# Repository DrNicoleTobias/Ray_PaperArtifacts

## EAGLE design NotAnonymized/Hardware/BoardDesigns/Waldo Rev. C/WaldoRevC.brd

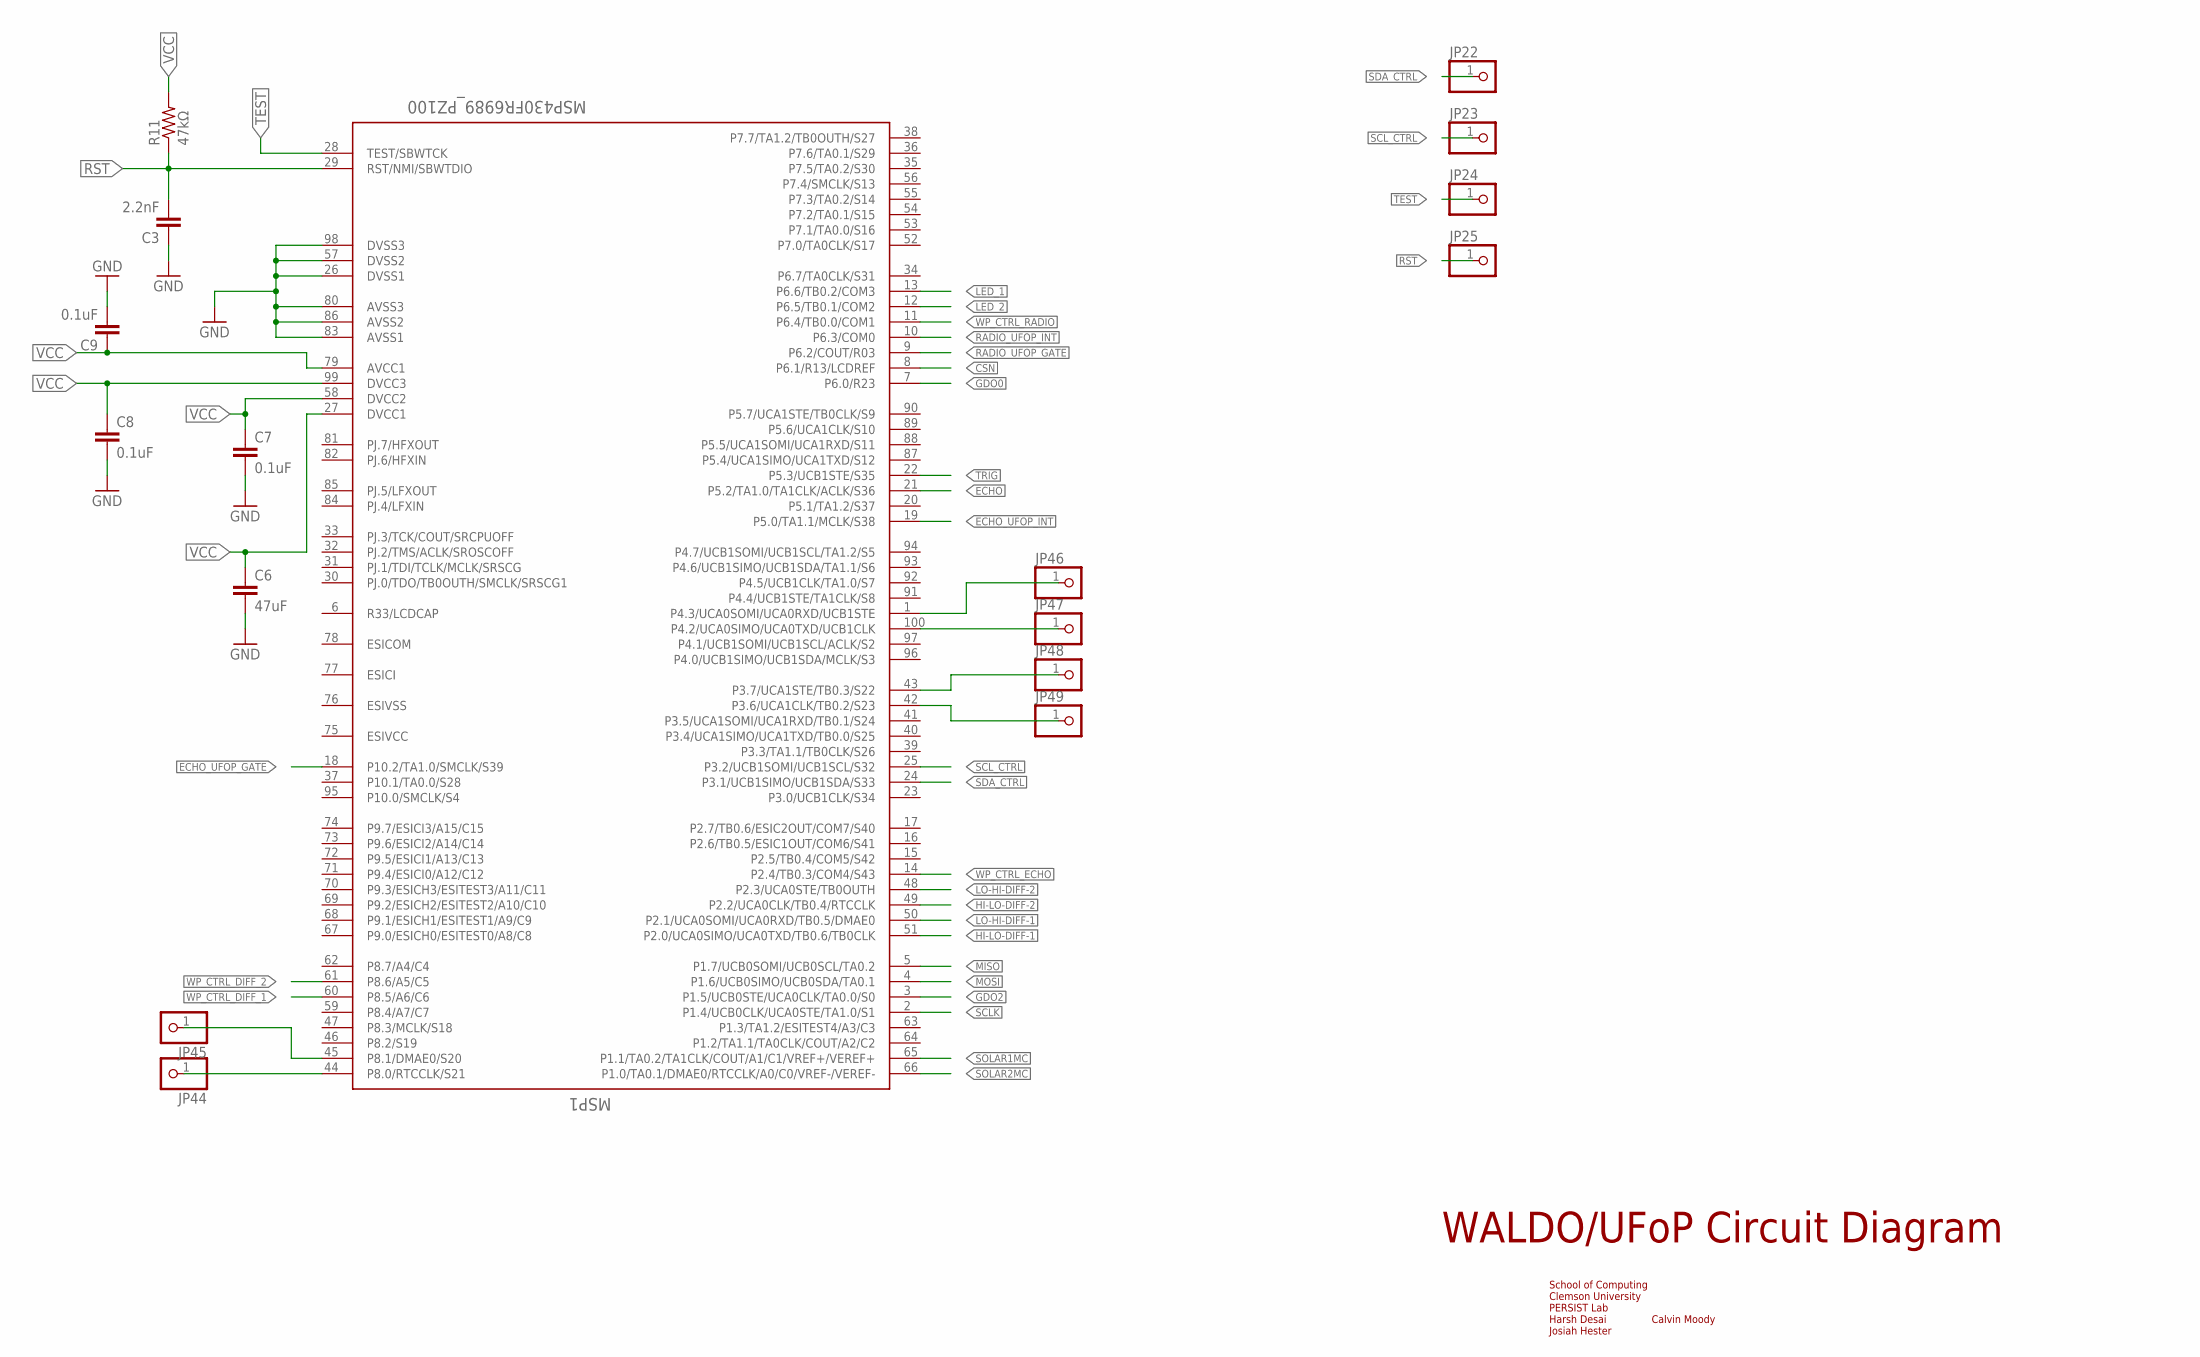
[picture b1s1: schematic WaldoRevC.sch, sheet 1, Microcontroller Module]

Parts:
C3: 2.2nF; 0805
C6: 47uF; 0805
C7, C8, C9: 0.1uF; 0805
JP22, JP23, JP24, JP25, JP44, JP45, JP46, JP47, JP48, JP49: PINHD-1X1; 1X01
MSP1: MSP430FR6989_PZ100; PZ100
R11: 47kΩ; 0805

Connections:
CSN: MSP1.8 (P6.1/R13/LCDREF); also elsewhere on the board
ECHO: MSP1.21 (P5.2/TA1.0/TA1CLK/ACLK/S36); also elsewhere on the board
ECHO_UFOP_GATE: MSP1.18 (P10.2/TA1.0/SMCLK/S39); also elsewhere on the board
ECHO_UFOP_INT: MSP1.19 (P5.0/TA1.1/MCLK/S38); also elsewhere on the board
GDO0: MSP1.7 (P6.0/R23); also elsewhere on the board
GDO2: MSP1.3 (P1.5/UCB0STE/UCA0CLK/TA0.0/S0); also elsewhere on the board
GND: C3.1, C6.2, C7.2, C8.2, C9.2, MSP1.26 (DVSS1), MSP1.57 (DVSS2), MSP1.80 (AVSS3), MSP1.83 (AVSS1), MSP1.86 (AVSS2), MSP1.98 (DVSS3); also elsewhere on the board
HI-LO-DIFF-1: MSP1.51 (P2.0/UCA0SIMO/UCA0TXD/TB0.6/TB0CLK); also elsewhere on the board
HI-LO-DIFF-2: MSP1.49 (P2.2/UCA0CLK/TB0.4/RTCCLK); also elsewhere on the board
LED_1: MSP1.13 (P6.6/TB0.2/COM3); also elsewhere on the board
LED_2: MSP1.12 (P6.5/TB0.1/COM2); also elsewhere on the board
LO-HI-DIFF-1: MSP1.50 (P2.1/UCA0SOMI/UCA0RXD/TB0.5/DMAE0); also elsewhere on the board
LO-HI-DIFF-2: MSP1.48 (P2.3/UCA0STE/TB0OUTH); also elsewhere on the board
MISO: MSP1.5 (P1.7/UCB0SOMI/UCB0SCL/TA0.2); also elsewhere on the board
MOSI: MSP1.4 (P1.6/UCB0SIMO/UCB0SDA/TA0.1); also elsewhere on the board
unnamed: JP44.1, MSP1.44 (P8.0/RTCCLK/S21)
unnamed: JP45.1, MSP1.45 (P8.1/DMAE0/S20)
unnamed: JP46.1, MSP1.1 (P4.3/UCA0SOMI/UCA0RXD/UCB1STE)
unnamed: JP47.1, MSP1.100 (P4.2/UCA0SIMO/UCA0TXD/UCB1CLK)
unnamed: JP49.1, MSP1.42 (P3.6/UCA1CLK/TB0.2/S23)
unnamed: JP48.1, MSP1.43 (P3.7/UCA1STE/TB0.3/S22)
RADIO_UFOP_GATE: MSP1.9 (P6.2/COUT/R03); also elsewhere on the board
RADIO_UFOP_INT: MSP1.10 (P6.3/COM0); also elsewhere on the board
RST: C3.2, JP25.1, MSP1.29 (RST/NMI/SBWTDIO), R11.1; also elsewhere on the board
SCLK: MSP1.2 (P1.4/UCB0CLK/UCA0STE/TA1.0/S1); also elsewhere on the board
SCL_CTRL: JP23.1, MSP1.25 (P3.2/UCB1SOMI/UCB1SCL/S32); also elsewhere on the board
SDA_CTRL: JP22.1, MSP1.24 (P3.1/UCB1SIMO/UCB1SDA/S33); also elsewhere on the board
SOLAR1MC: MSP1.65 (P1.1/TA0.2/TA1CLK/COUT/A1/C1/VREF+/VERE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); also elsewhere on the board
SOLAR2MC: MSP1.66 (P1.0/TA0.1/DMAE0/RTCCLK/A0/C0/VREF-/VER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); also elsewhere on the board
TEST: JP24.1, MSP1.28 (TEST/SBWTCK); also elsewhere on the board
TRIG: MSP1.22 (P5.3/UCB1STE/S35); also elsewhere on the board
VCC: C6.1, C7.1, C8.1, C9.1, MSP1.27 (DVCC1), MSP1.58 (DVCC2), MSP1.79 (AVCC1), MSP1.99 (DVCC3), R11.2; also elsewhere on the board
WP_CTRL_DIFF_1: MSP1.60 (P8.5/A6/C6); also elsewhere on the board
WP_CTRL_DIFF_2: MSP1.61 (P8.6/A5/C5); also elsewhere on the board
WP_CTRL_ECHO: MSP1.14 (P2.4/TB0.3/COM4/S43); also elsewhere on the board
WP_CTRL_RADIO: MSP1.11 (P6.4/TB0.0/COM1); also elsewhere on the board

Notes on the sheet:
WALDO/UFoP Circuit Diagram
School of Computing Clemson University PERSIST Lab Harsh Desai Calvin Moody Josiah Hester

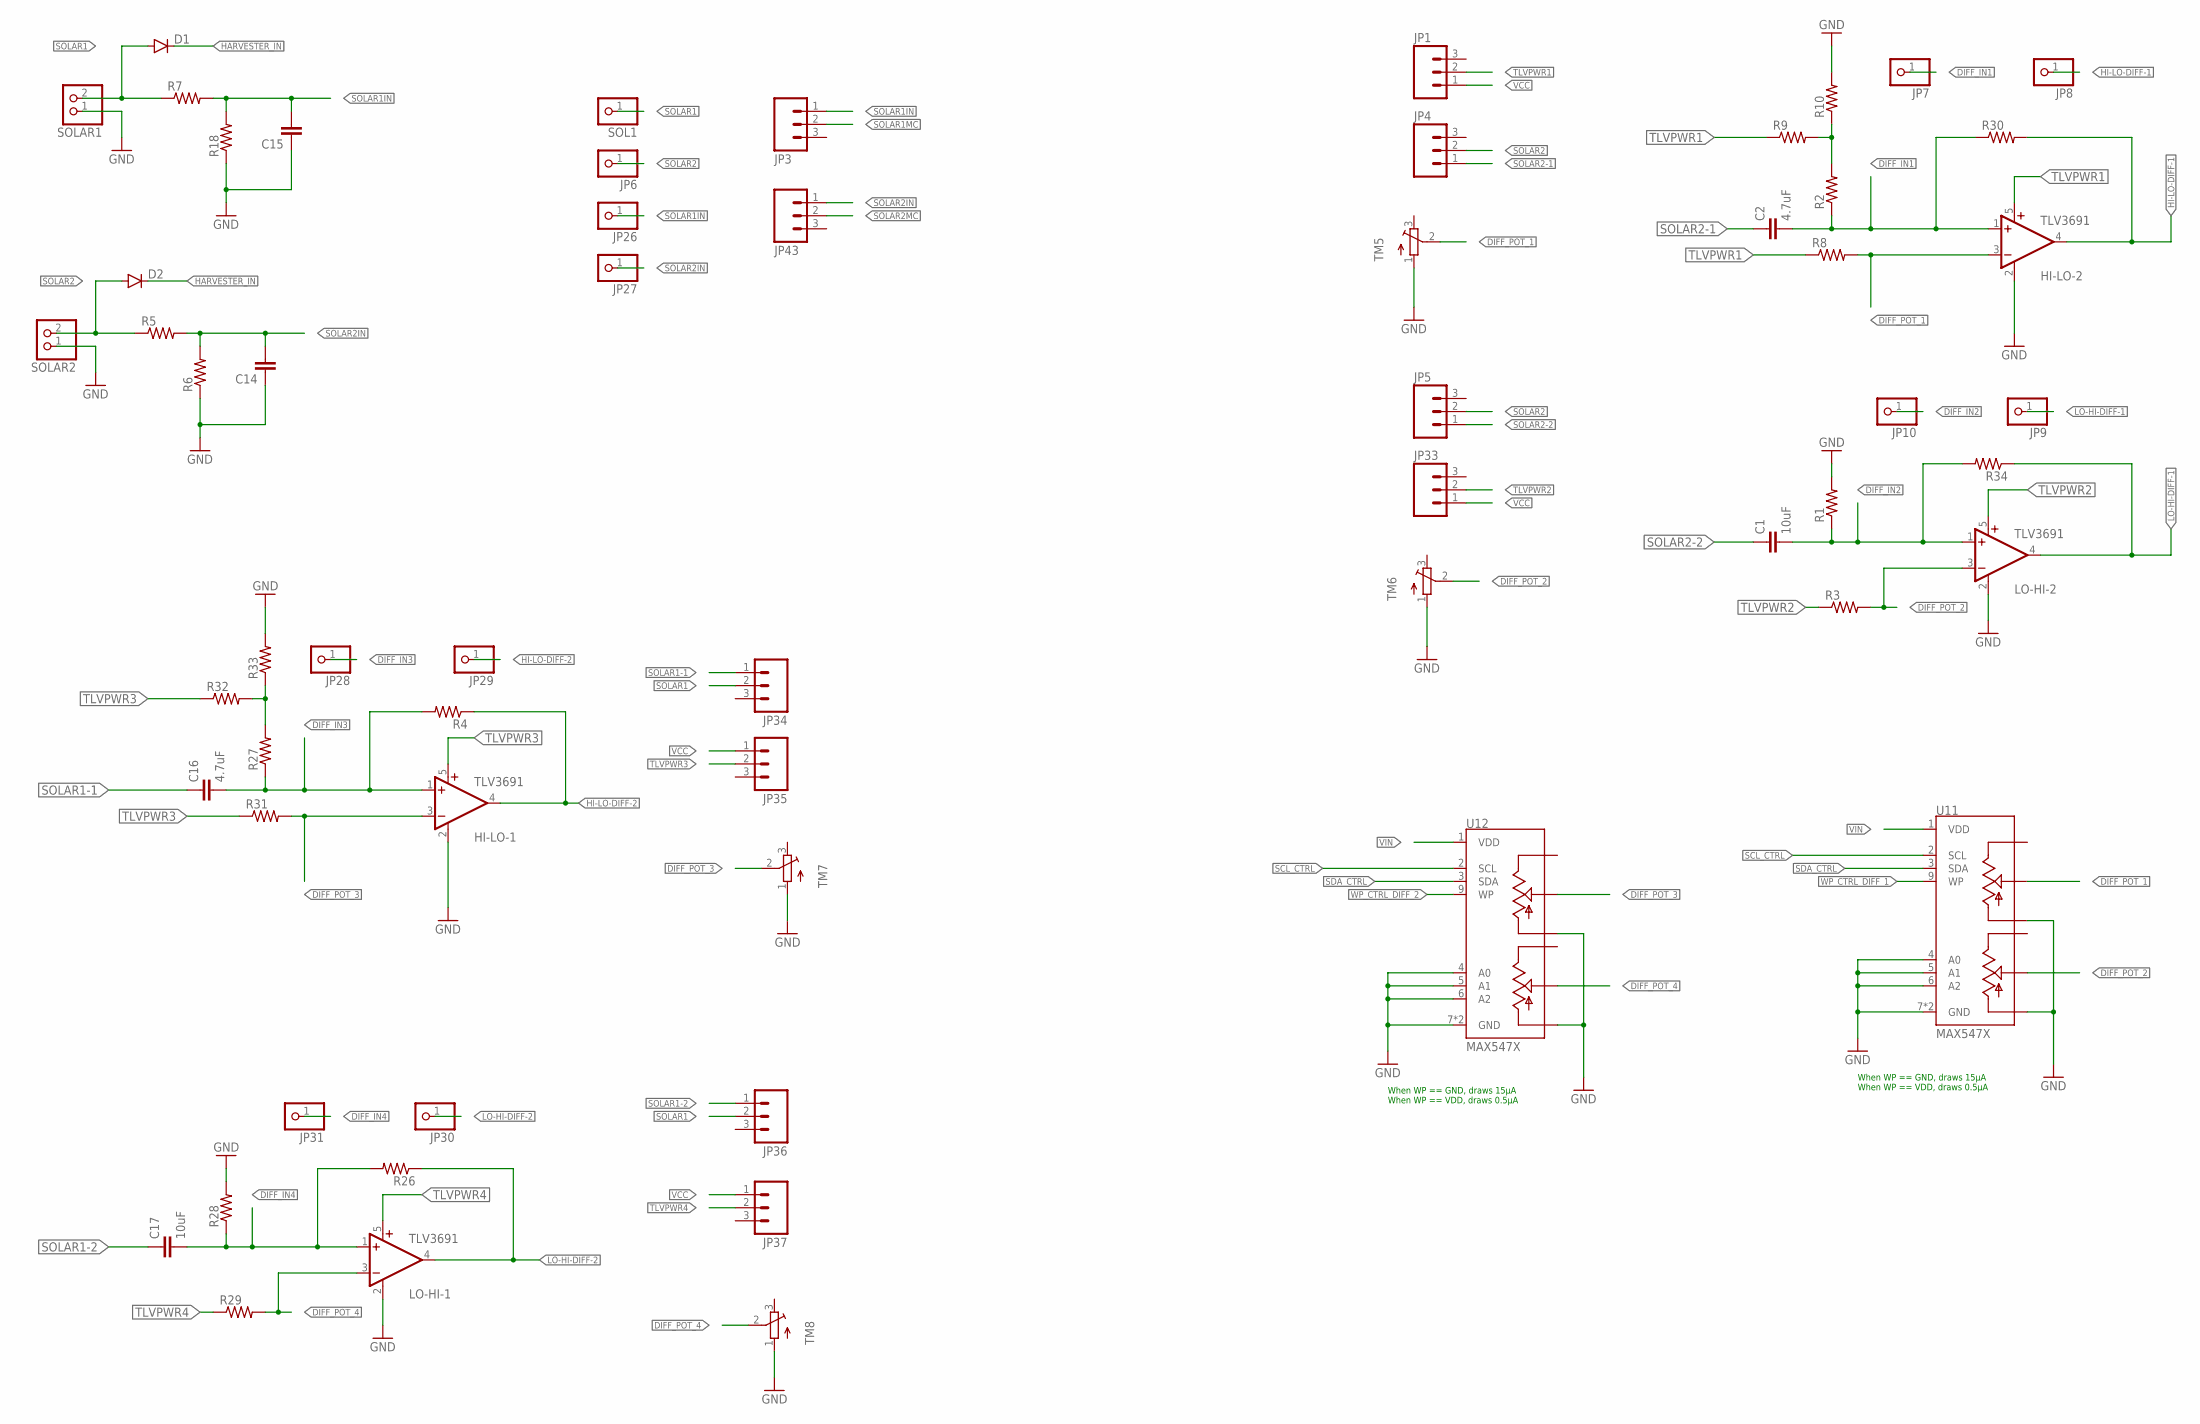
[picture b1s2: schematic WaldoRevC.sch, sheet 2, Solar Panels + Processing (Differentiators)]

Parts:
C1, C17: 10uF; 0805
C2, C16: 4.7uF; 0805
C14, C15: CAP0805; 0805
D1, D2: DIODESOD523; SOD523
HI-LO-1, HI-LO-2: TLV3691; SC70-5
JP1, JP3, JP4, JP5, JP33, JP34, JP35, JP36, JP37, JP43: M03; 1X03-1.27MM
JP6, JP7, JP8, JP9, JP10, JP26, JP27, JP28, JP29, JP30, JP31: PINHD-1X1; 1X01
LO-HI-1, LO-HI-2: TLV3691; SC70-5
R1, R2, R3, R4, R5, R6, R7, R8, R9, R10, R18, R26, R27, R28, R29, R30, R31, R32, R33, R34: RESISTOR0805-RES; 0805
SOL1: PINHD-1X1; 1X01
SOLAR1, SOLAR2: PINHD-1X2; 1X02
TM5, TM6, TM7, TM8: TRIMPOTTC33X; TC33X
U11, U12: MAX547X; QFN16; DIGIKEY MAX5479ETE+-ND

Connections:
DIFF_IN1: C2.2, HI-LO-2.1 (+IN), JP7.1, R2.1, R30.1
DIFF_IN2: C1.2, JP10.1, LO-HI-2.1 (+IN), R1.1, R34.2
DIFF_IN3: C16.2, HI-LO-1.1 (+IN), JP28.1, R4.2, R27.1
DIFF_IN4: C17.2, JP31.1, LO-HI-1.1 (+IN), R26.2, R28.1
DIFF_POT_1: HI-LO-2.3 (-IN), R8.2, TM5.2 (S), U11.14 (WA)
DIFF_POT_2: LO-HI-2.3 (-IN), R3.2, TM6.2 (S), U11.11 (WB)
DIFF_POT_3: HI-LO-1.3 (-IN), R31.2, TM7.2 (S), U12.14 (WA)
DIFF_POT_4: LO-HI-1.3 (-IN), R29.2, TM8.2 (S), U12.11 (WB)
GND: C14.1, C15.1, HI-LO-1.2 (GND), HI-LO-2.2 (GND), LO-HI-1.2 (GND), LO-HI-2.2 (GND), R1.2, R6.1, R10.2, R18.1, R28.2, R33.2, SOLAR1.1, SOLAR2.1, TM5.1 (A), TM6.1 (A), TM7.1 (A), TM8.1 (A), U11.4 (A0), U11.5 (A1), U11.6 (A2), U11.7 (GND), U11.10 (LB), U11.13 (LA), U11.TH (GND), U12.4 (A0), U12.5 (A1), U12.6 (A2), U12.7 (GND), U12.10 (LB), U12.13 (LA), U12.TH (GND); also elsewhere on the board
HARVESTER_IN: D1.C, D2.C; also elsewhere on the board
HI-LO-DIFF-1: HI-LO-2.4 (OUT), JP8.1, R30.2; also elsewhere on the board
HI-LO-DIFF-2: HI-LO-1.4 (OUT), JP29.1, R4.1; also elsewhere on the board
LO-HI-DIFF-1: JP9.1, LO-HI-2.4 (OUT), R34.1; also elsewhere on the board
LO-HI-DIFF-2: JP30.1, LO-HI-1.4 (OUT), R26.1; also elsewhere on the board
unnamed: R27.2, R32.2, R33.1
unnamed: R2.2, R9.2, R10.1
SCL_CTRL: U11.2 (SCL), U12.2 (SCL); also elsewhere on the board
SDA_CTRL: U11.3 (SDA), U12.3 (SDA); also elsewhere on the board
SOLAR1: D1.A, JP34.2, JP36.2, R7.1, SOL1.1, SOLAR1.2
SOLAR1-1: C16.1, JP34.1
SOLAR1-2: C17.1, JP36.1
SOLAR1IN: C15.2, JP3.1, JP26.1, R7.2, R18.2
SOLAR1MC: JP3.2; also elsewhere on the board
SOLAR2: D2.A, JP4.2, JP5.2, JP6.1, R5.1, SOLAR2.2
SOLAR2-1: C2.1, JP4.1
SOLAR2-2: C1.1, JP5.1
SOLAR2IN: C14.2, JP27.1, JP43.1, R5.2, R6.2
SOLAR2MC: JP43.2; also elsewhere on the board
TLVPWR1: HI-LO-2.5 (V+), JP1.2, R8.1, R9.1
TLVPWR2: JP33.2, LO-HI-2.5 (V+), R3.1
TLVPWR3: HI-LO-1.5 (V+), JP35.2, R31.1, R32.1
TLVPWR4: JP37.2, LO-HI-1.5 (V+), R29.1
VCC: JP1.1, JP33.1, JP35.1, JP37.1; also elsewhere on the board
VIN: U11.1 (VDD), U12.1 (VDD); also elsewhere on the board
WP_CTRL_DIFF_1: U11.9 (WP); also elsewhere on the board
WP_CTRL_DIFF_2: U12.9 (WP); also elsewhere on the board

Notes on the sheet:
When WP == GND, draws 15µA When WP == VDD, draws 0.5µA

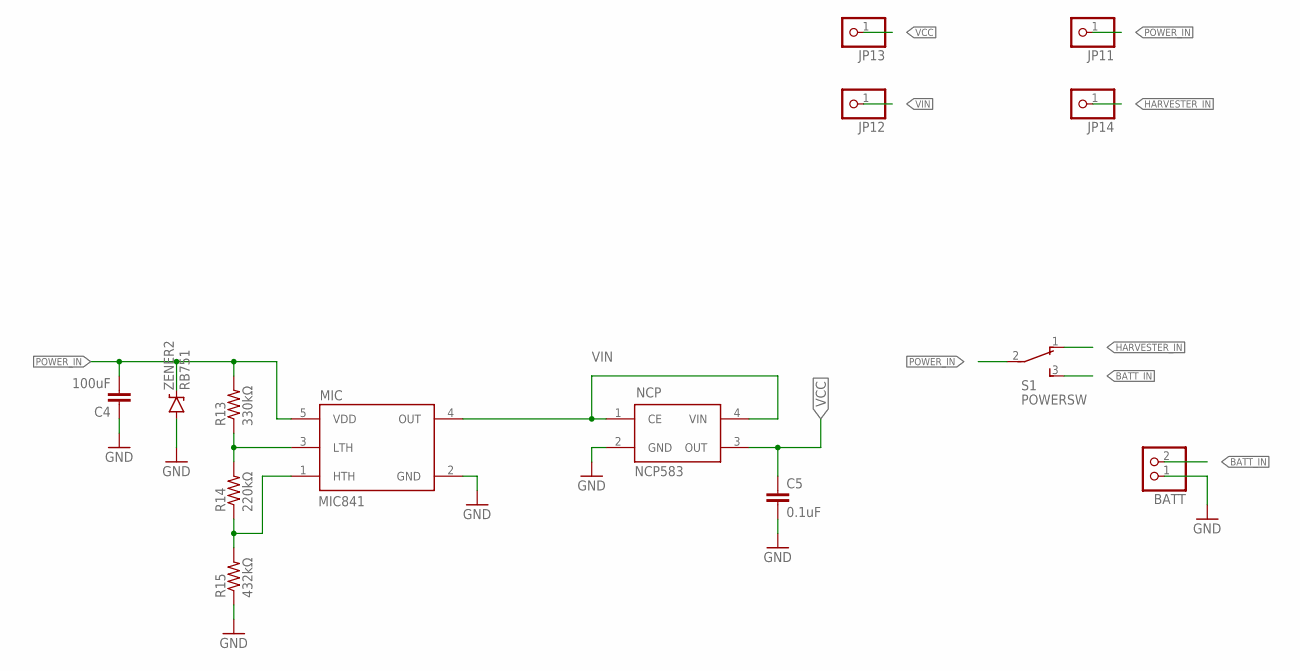
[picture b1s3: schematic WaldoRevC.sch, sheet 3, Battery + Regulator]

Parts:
BATT: PINHD-1X2; 1X02
C4: 100uF; 0805
C5: 0.1uF; 0805
JP11, JP12, JP13, JP14: PINHD-1X1; 1X01
MIC: MIC841; SC70-5
NCP: NCP583; SC82-AB_1PRIMARY
R13: 330kΩ; 0805
R14: 220kΩ; 0805
R15: 432kΩ; 0805
S1: POWERSW; TL3XYO
ZENER2: RB751; SOD-523

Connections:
BATT_IN: BATT.2, S1.3 (S)
GND: BATT.1, C4.1, C5.2, MIC.2 (GND), NCP.2 (GND), R15.1, ZENER2.ANODE (A); also elsewhere on the board
HARVESTER_IN: JP14.1, S1.1 (O); also elsewhere on the board
unnamed: MIC.3 (LTH), R13.1, R14.2
unnamed: MIC.1 (HTH), R14.1, R15.2
POWER_IN: C4.2, JP11.1, MIC.5 (VDD), R13.2, S1.2, ZENER2.CATHODE (C)
VCC: C5.1, JP13.1, NCP.3 (OUT); also elsewhere on the board
VIN: JP12.1, MIC.4 (OUT), NCP.1 (CE), NCP.4 (VIN); also elsewhere on the board

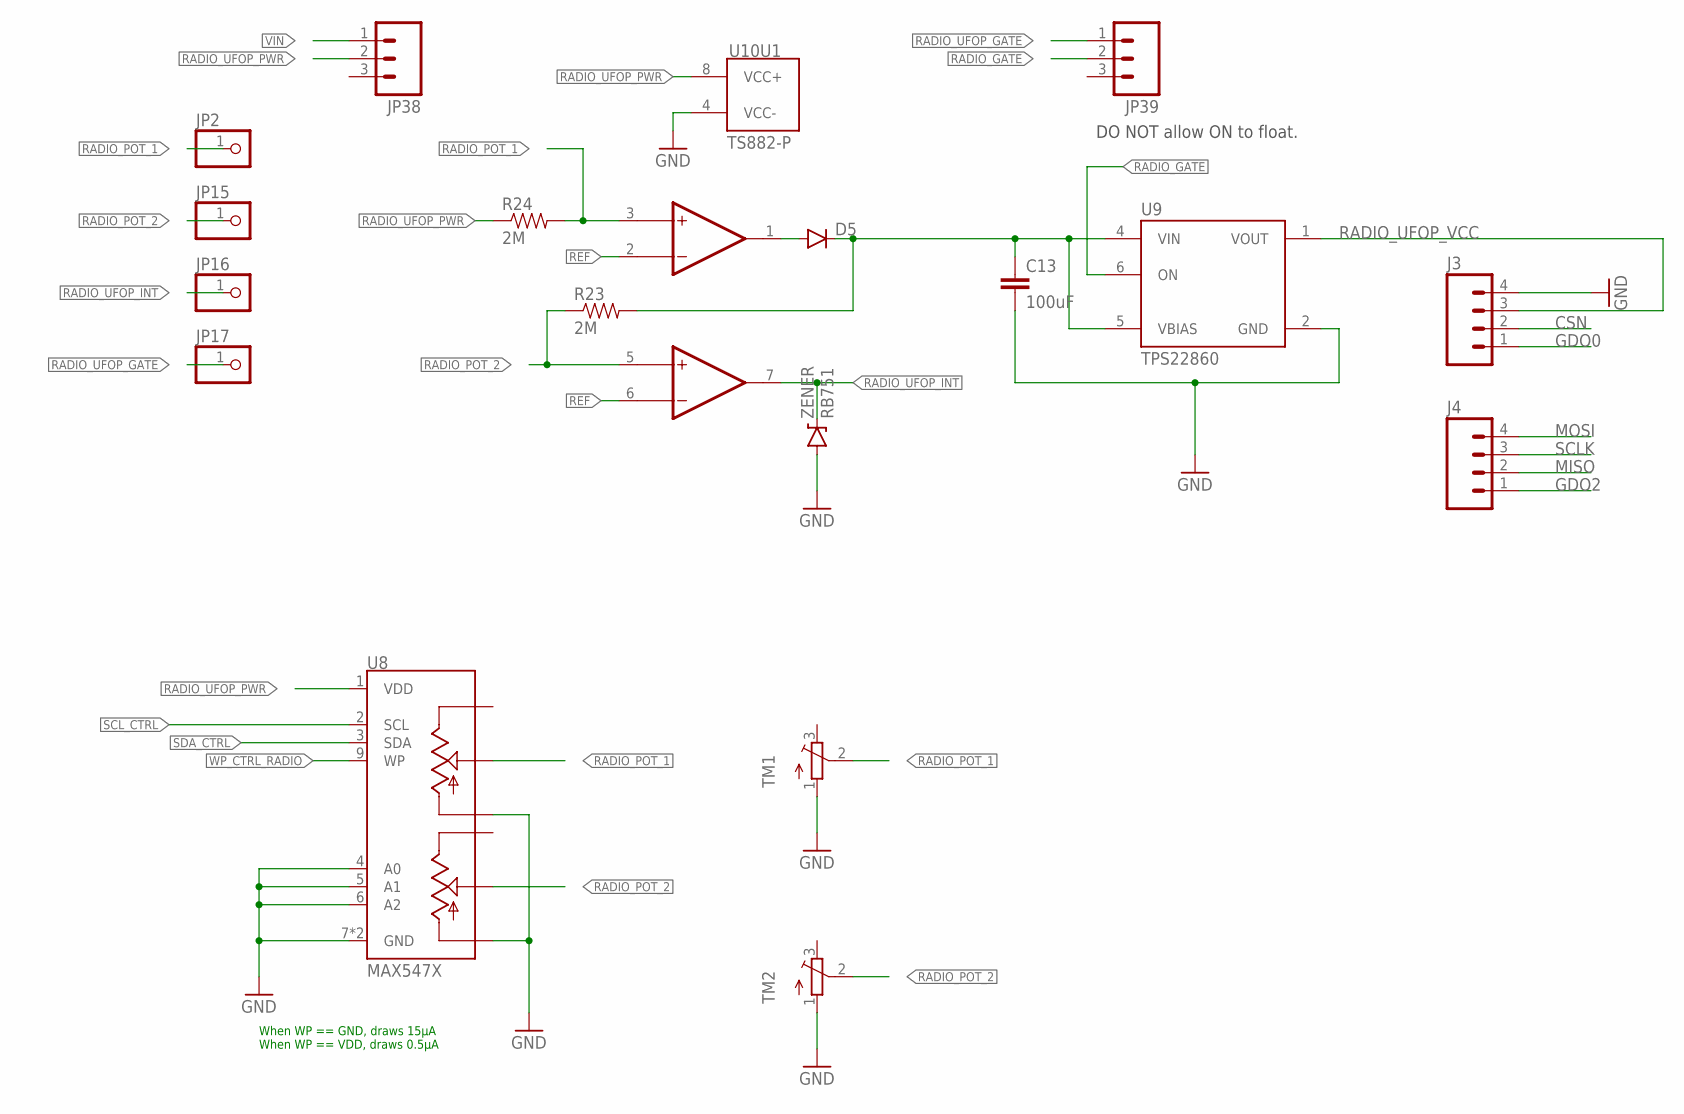
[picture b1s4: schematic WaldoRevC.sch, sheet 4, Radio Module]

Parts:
C13: 100uF; 0805; DIGIKEY 490-9969-1-ND
D5: DIODESOD523; SOD523
J3, J4: M04PTH; 1X04
JP2, JP15, JP16, JP17: PINHD-1X1; 1X01
JP38, JP39: M03; 1X03-1.27MM
R23: 2M; 0805; DIGIKEY 311-2.00MHRCT-ND
R24: 2M; 0805
TM1, TM2: TRIMPOTTC33X; TC33X
U8: MAX547X; QFN16; DIGIKEY MAX5479ETE+-ND
U9: TPS22860; TSOT23-6
U10: TS882-P; UDFN8; DIGIKEY 497-14073-1-ND
ZENER: RB751; SOD-523

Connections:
CSN: J3.2; also elsewhere on the board
GDO0: J3.1; also elsewhere on the board
GDO2: J4.1; also elsewhere on the board
GND: C13.2, J3.4, TM1.1 (A), TM2.1 (A), U8.4 (A0), U8.5 (A1), U8.6 (A2), U8.7 (GND), U8.10 (LB), U8.13 (LA), U8.TH (GND), U9.2 (GND), U10.4 (VCC-), ZENER.ANODE (A); also elsewhere on the board
MISO: J4.2; also elsewhere on the board
MOSI: J4.4; also elsewhere on the board
unnamed: C13.1, D5.C, R23.2, U9.4 (VIN), U9.5 (VBIAS)
unnamed: D5.A, U10.1 (OUT1)
RADIO_GATE: JP39.2, U9.6 (ON)
RADIO_POT_1: JP2.1, R24.2, TM1.2 (S), U8.14 (WA), U10.3 (IN1+)
RADIO_POT_2: JP15.1, R23.1, TM2.2 (S), U8.11 (WB), U10.5 (IN1+)
RADIO_UFOP_GATE: JP17.1, JP39.1; also elsewhere on the board
RADIO_UFOP_INT: JP16.1, U10.7 (OUT1), ZENER.CATHODE (C); also elsewhere on the board
RADIO_UFOP_PWR: JP38.2, R24.1, U8.1 (VDD), U10.8 (VCC+)
RADIO_UFOP_VCC: J3.3, U9.1 (VOUT)
REF: U10.2 (IN1-), U10.6 (IN1-); also elsewhere on the board
SCLK: J4.3; also elsewhere on the board
SCL_CTRL: U8.2 (SCL); also elsewhere on the board
SDA_CTRL: U8.3 (SDA); also elsewhere on the board
VIN: JP38.1; also elsewhere on the board
WP_CTRL_RADIO: U8.9 (WP); also elsewhere on the board

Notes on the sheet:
DO NOT allow ON to float.
When WP == GND, draws 15µA When WP == VDD, draws 0.5µA

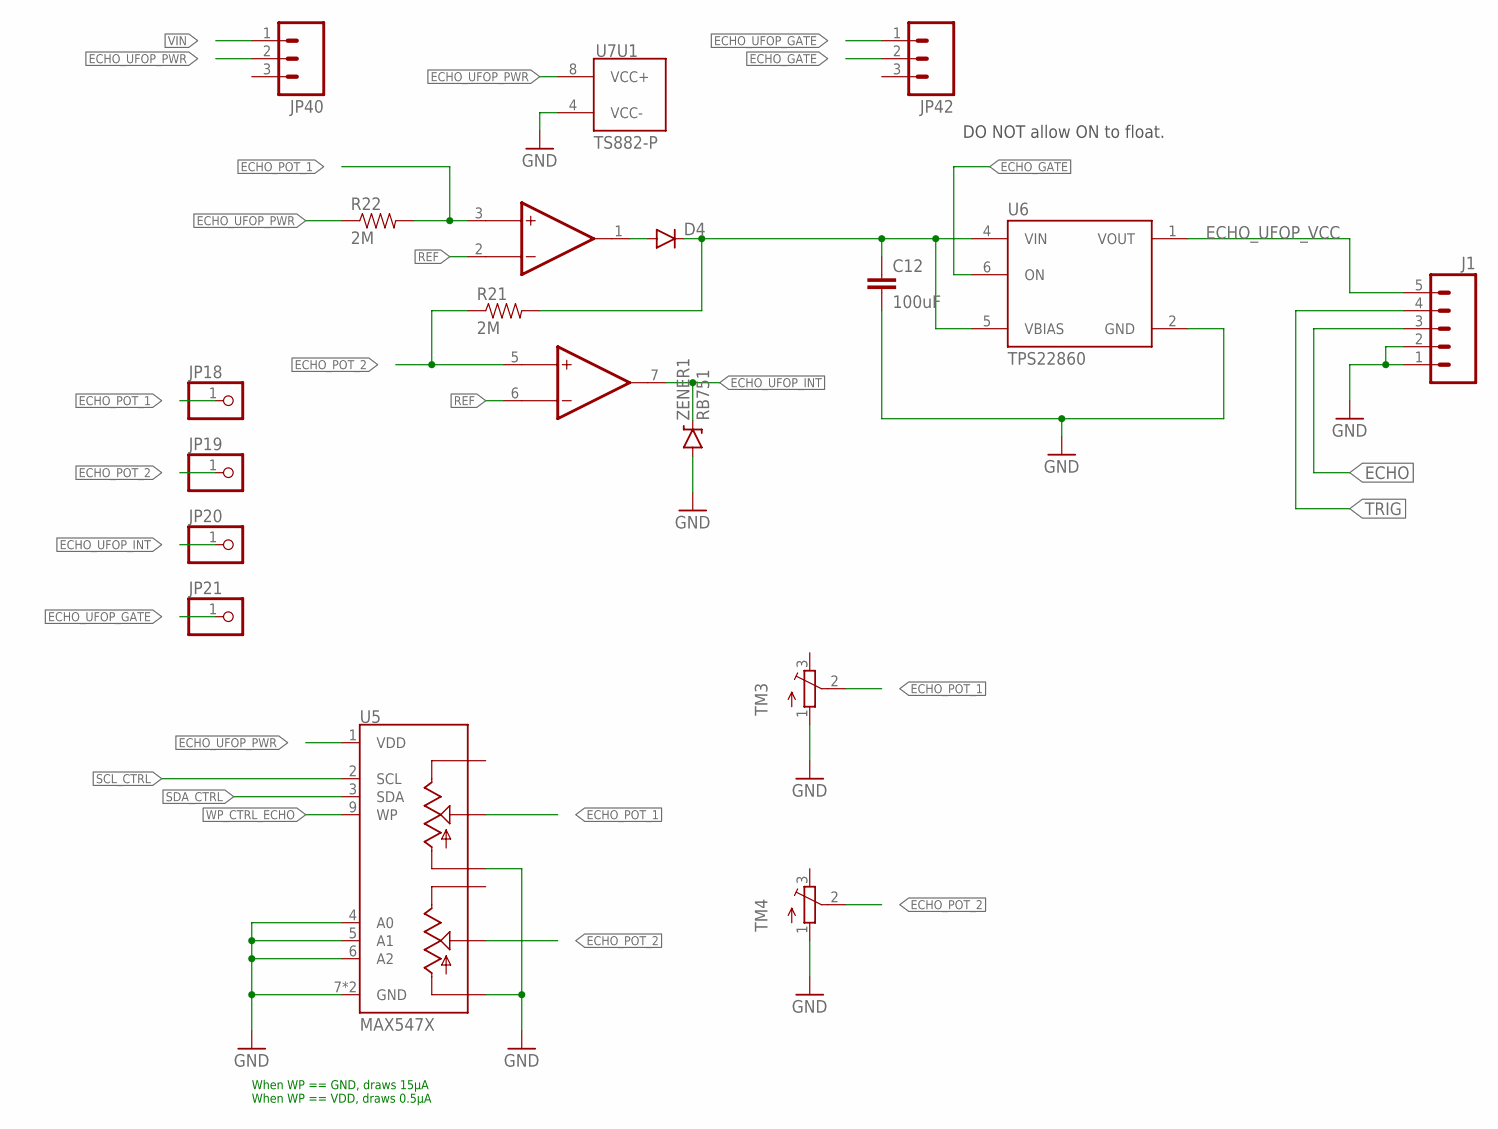
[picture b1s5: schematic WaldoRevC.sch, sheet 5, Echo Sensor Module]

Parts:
C12: 100uF; 0805; DIGIKEY 490-9969-1-ND
D4: DIODESOD523; SOD523
J1: M05PTH; 1X05
JP18, JP19, JP20, JP21: PINHD-1X1; 1X01
JP40, JP42: M03; 1X03-1.27MM
R21: 2M; 0805; DIGIKEY 311-2.00MHRCT-ND
R22: 2M; 0805
TM3, TM4: TRIMPOTTC33X; TC33X
U5: MAX547X; QFN16; DIGIKEY MAX5479ETE+-ND
U6: TPS22860; TSOT23-6
U7: TS882-P; UDFN8; DIGIKEY 497-14073-1-ND
ZENER1: RB751; SOD-523

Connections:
ECHO: J1.3; also elsewhere on the board
ECHO_GATE: JP42.2, U6.6 (ON)
ECHO_POT_1: JP18.1, R22.2, TM3.2 (S), U5.14 (WA), U7.3 (IN1+)
ECHO_POT_2: JP19.1, R21.1, TM4.2 (S), U5.11 (WB), U7.5 (IN1+)
ECHO_UFOP_GATE: JP21.1, JP42.1; also elsewhere on the board
ECHO_UFOP_INT: JP20.1, U7.7 (OUT1), ZENER1.CATHODE (C); also elsewhere on the board
ECHO_UFOP_PWR: JP40.2, R22.1, U5.1 (VDD), U7.8 (VCC+)
ECHO_UFOP_VCC: J1.5, U6.1 (VOUT)
GND: C12.2, J1.1, J1.2, TM3.1 (A), TM4.1 (A), U5.4 (A0), U5.5 (A1), U5.6 (A2), U5.7 (GND), U5.10 (LB), U5.13 (LA), U5.TH (GND), U6.2 (GND), U7.4 (VCC-), ZENER1.ANODE (A); also elsewhere on the board
unnamed: C12.1, D4.C, R21.2, U6.4 (VIN), U6.5 (VBIAS)
unnamed: D4.A, U7.1 (OUT1)
REF: U7.2 (IN1-), U7.6 (IN1-); also elsewhere on the board
SCL_CTRL: U5.2 (SCL); also elsewhere on the board
SDA_CTRL: U5.3 (SDA); also elsewhere on the board
TRIG: J1.4; also elsewhere on the board
VIN: JP40.1; also elsewhere on the board
WP_CTRL_ECHO: U5.9 (WP); also elsewhere on the board

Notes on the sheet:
DO NOT allow ON to float.
When WP == GND, draws 15µA When WP == VDD, draws 0.5µA

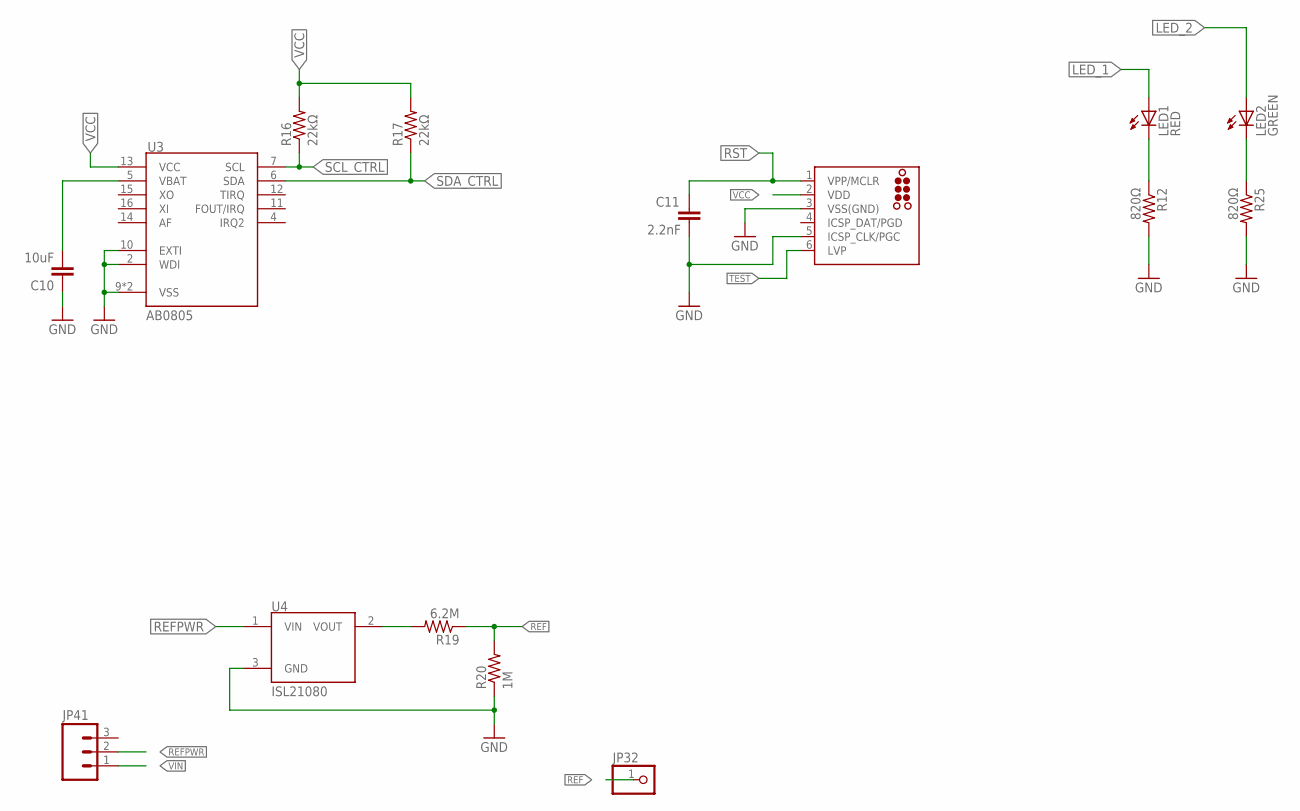
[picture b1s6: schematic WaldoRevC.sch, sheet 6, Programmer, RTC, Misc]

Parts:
C10: 10uF; 0805
C11: 2.2nF; 0805
J2: TC2030-MCP-NL
JP32: PINHD-1X1; 1X01
JP41: M03; 1X03-1.27MM
LED1: RED; CHIP-LED0805
LED2: GREEN; CHIP-LED0805
R12, R25: 820Ω; 0805
R16, R17: 22kΩ; 0805
R19: 6.2M; 0805; DIGIKEY 541-6.20MHCT-ND
R20: 1M; 0805; DIGIKEY 311-1.00MHRCT-ND
U3: AB0805; QFN16
U4: ISL21080; SOT-23; DIGIKEY ISL21080DIH309Z-TKCT-ND

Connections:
GND: C10.1, C11.2, J2.3 (VSS(GND)), J2.5 (ICSP_CLK/PGC), R12.2, R20.1, R25.2, U3.2 (WDI), U3.9 (VSS), U3.10 (EXTI), U3.TH (VSS), U4.3 (GND); also elsewhere on the board
LED_1: LED1.A; also elsewhere on the board
LED_2: LED2.A; also elsewhere on the board
unnamed: LED1.C, R12.1
unnamed: LED2.C, R25.1
unnamed: C10.2, U3.5 (VBAT)
unnamed: R19.2, U4.2 (VOUT)
REF: JP32.1, R19.1, R20.2; also elsewhere on the board
REFPWR: JP41.2, U4.1 (VIN)
RST: C11.1, J2.1 (VPP/MCLR); also elsewhere on the board
SCL_CTRL: R16.1, U3.7 (SCL); also elsewhere on the board
SDA_CTRL: R17.1, U3.6 (SDA); also elsewhere on the board
TEST: J2.6 (LVP); also elsewhere on the board
VCC: J2.2 (VDD), R16.2, R17.2, U3.13 (VCC); also elsewhere on the board
VIN: JP41.1; also elsewhere on the board

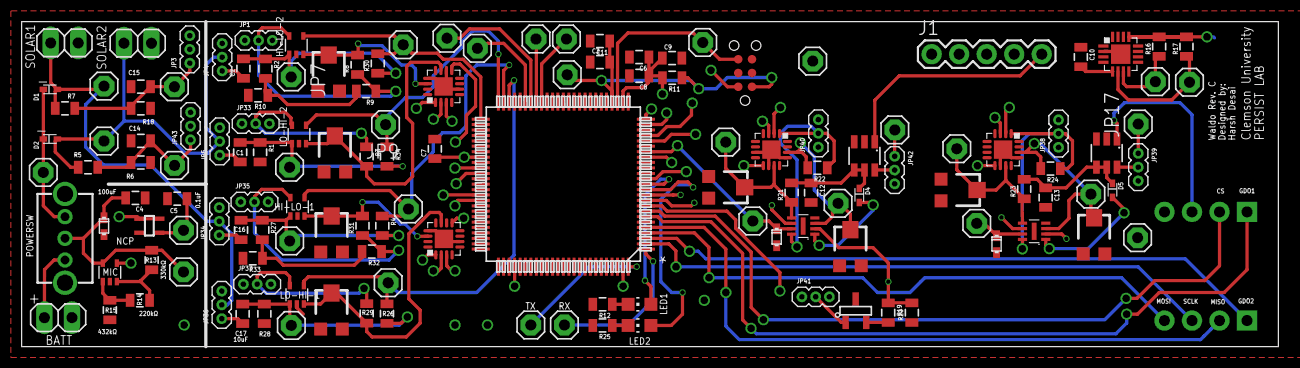
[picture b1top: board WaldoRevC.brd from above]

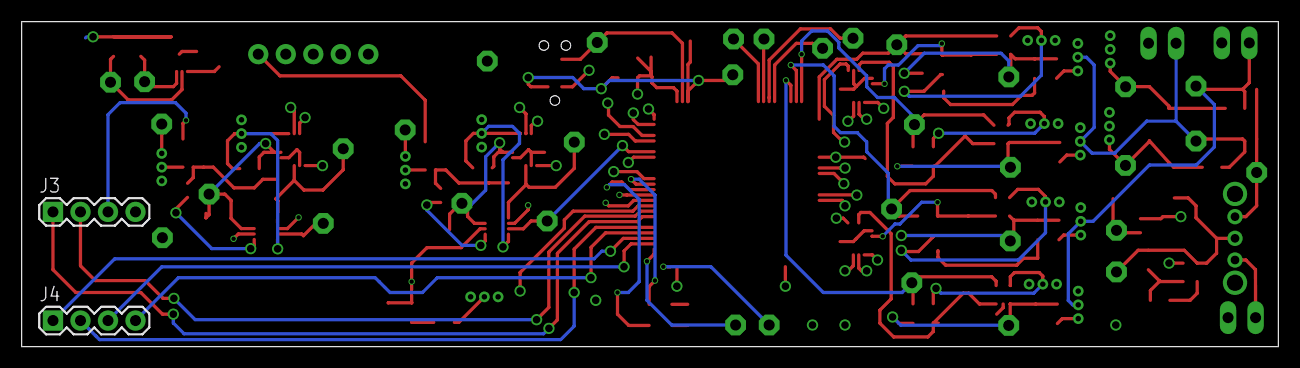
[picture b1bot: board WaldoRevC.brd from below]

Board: 4 copper layers, 116.0 x 30.0 mm, 143 parts (2 on the bottom side), 84 nets.

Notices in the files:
parts and their libraries:
SparkFun-Capacitors: Licensing: Creative Commons ShareAlike 4.0 International - https://creativecommons.org/licenses/by-sa/4.0
tag-connect_msp430: ©2009 ROFA.cz - modified and updated by Robert Darlington ‹rdarlington@gmail.com›
